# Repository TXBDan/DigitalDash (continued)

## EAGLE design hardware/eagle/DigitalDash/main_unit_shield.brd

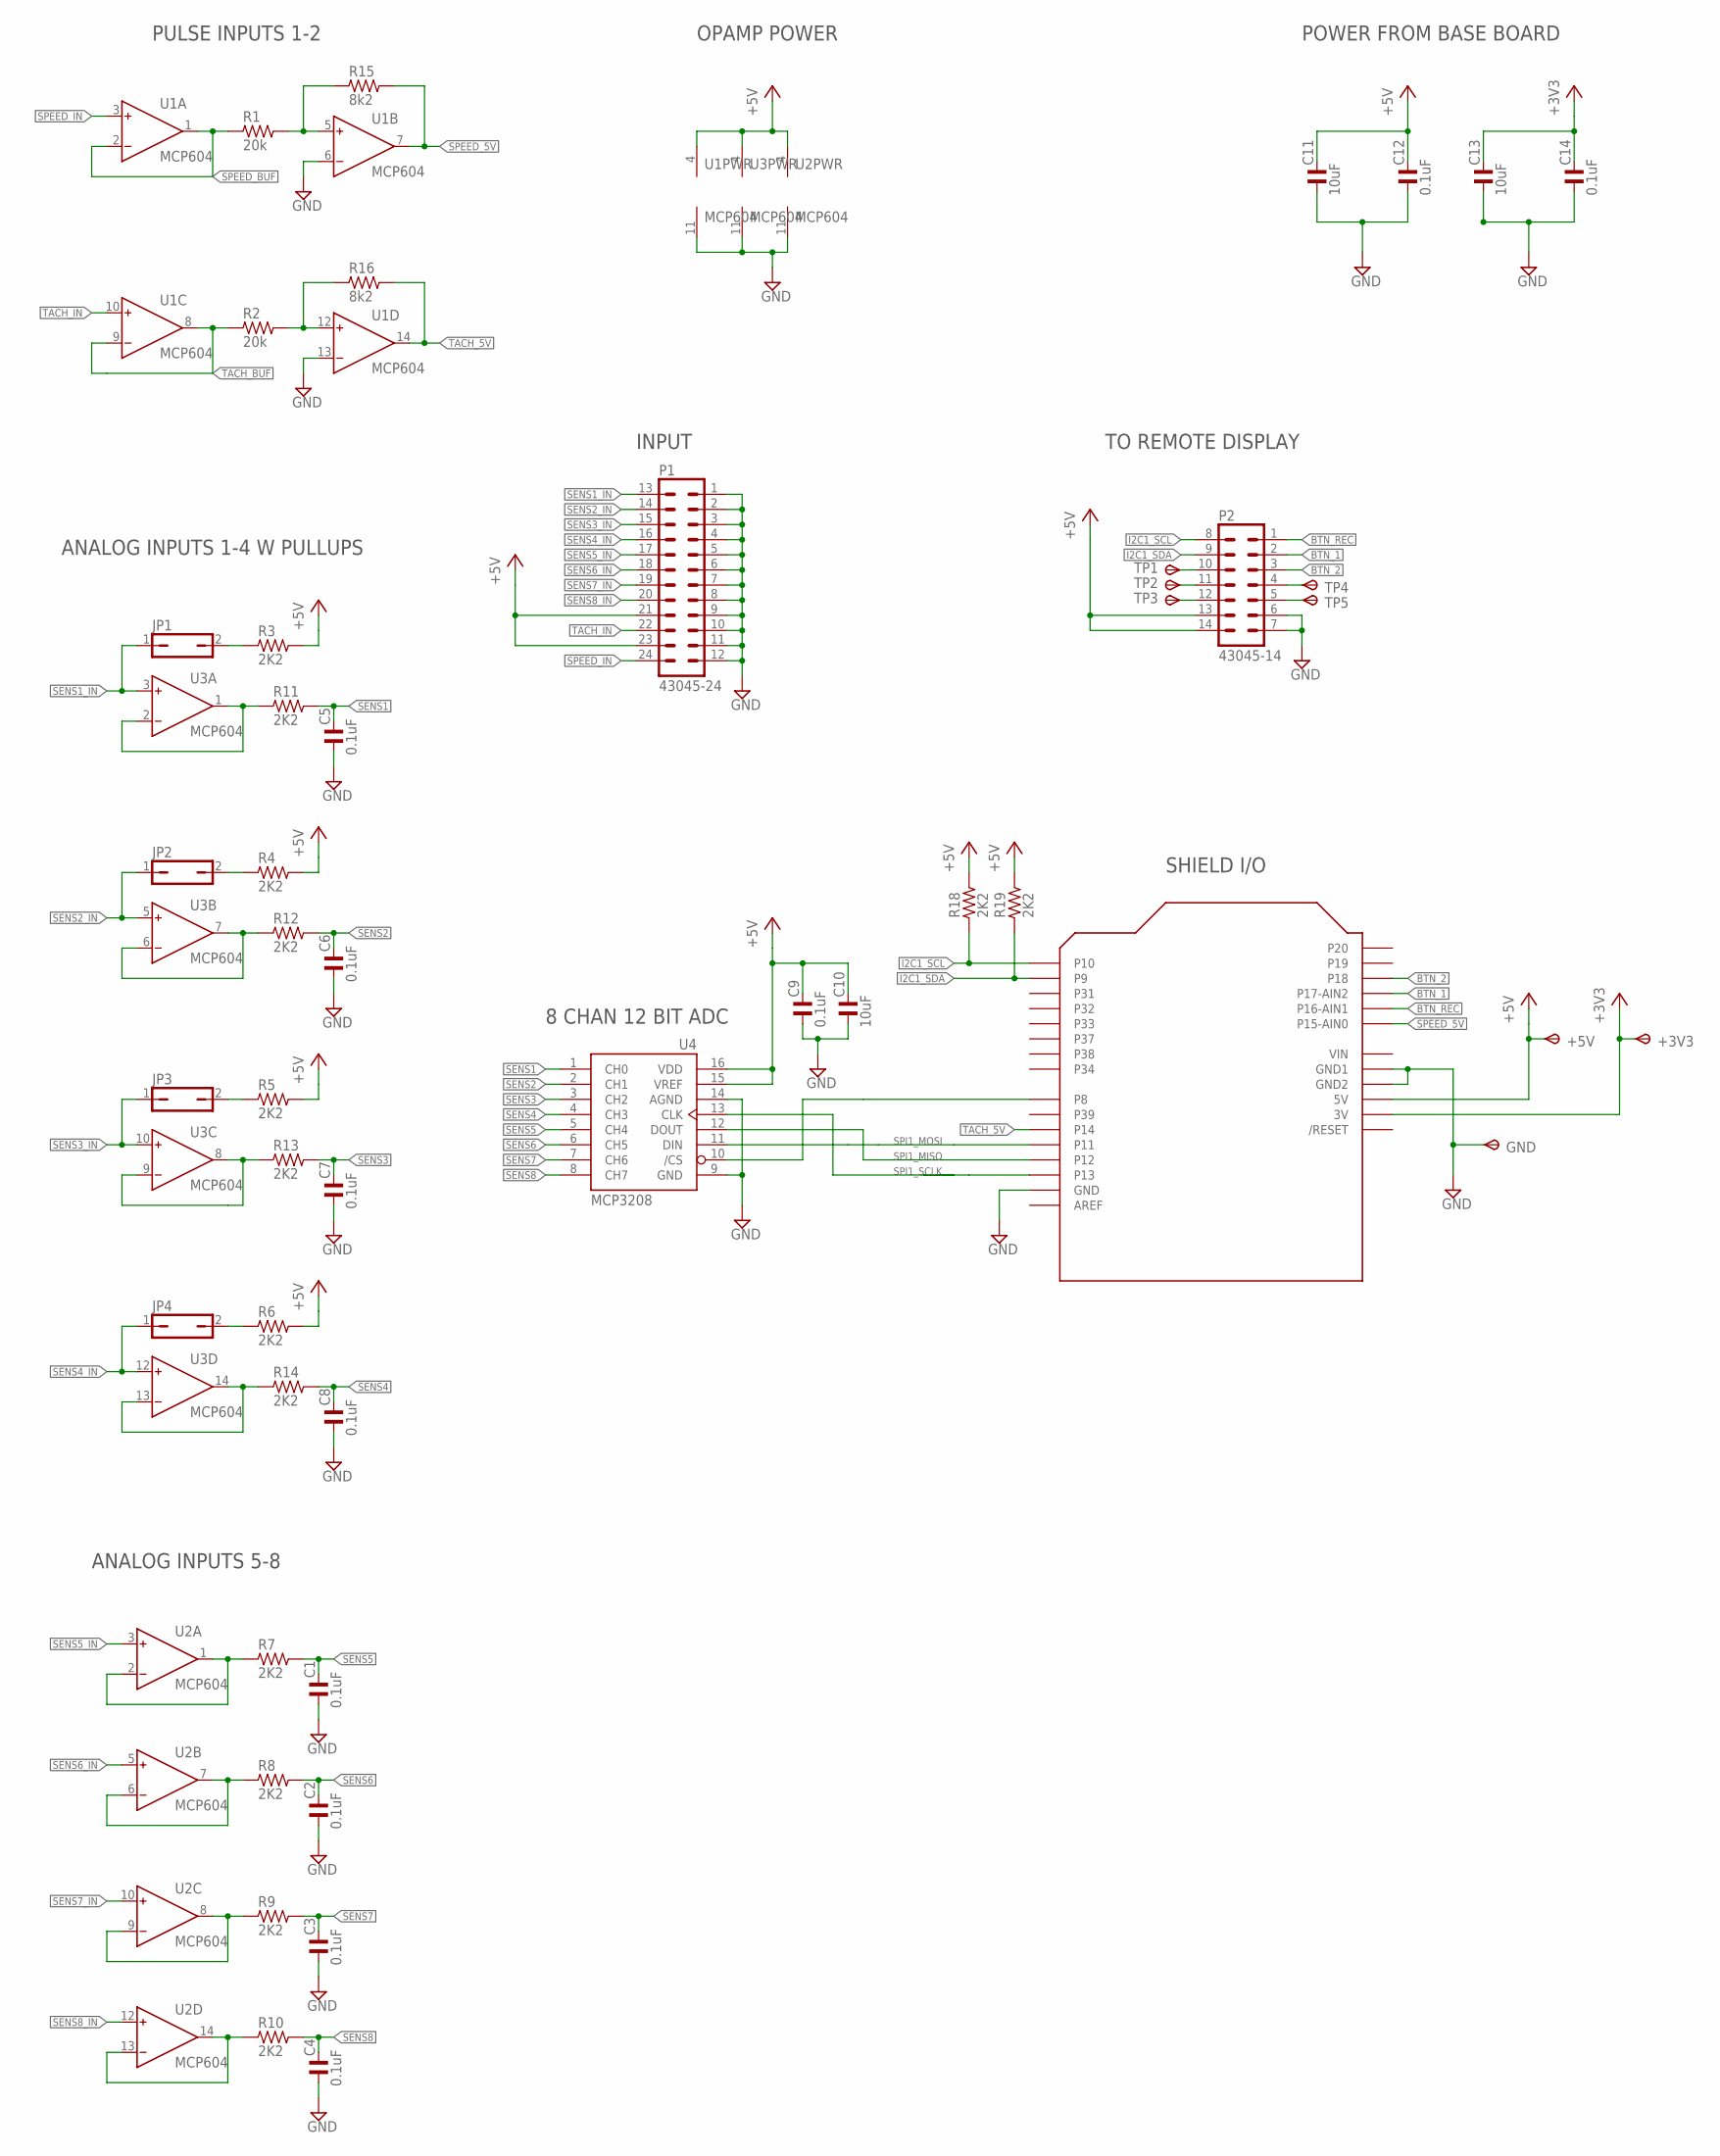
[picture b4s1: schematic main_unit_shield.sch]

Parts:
+3V3, +5V: TPSPAD1-13; P1-13
C1, C2, C3, C4, C5, C6, C7, C8, C9, C12, C14: 0.1uF; C0805; MPN C2012X7R1H104K085AA
C10, C11, C13: 10uF; C0805; MPN C2012X5R1E106K125AB
GND: TPSPAD1-13; P1-13
JP1, JP2, JP3, JP4: JP1Q; JP1; MPN 969102-0000-DA
P1: 43045-24; MPN 43045-2400
P2: 43045-14; MPN 43045-1400
R1, R2: 20k; R0805; MPN CRCW080520K0FKEA
R3, R4, R5, R6, R7, R8, R9, R10, R11, R12, R13, R14, R18, R19: 2K2; R0805; MPN CRCW08052K20FKEA
R15, R16: 8k2; R0805; MPN CRCW08058K20FKEAHP
TP1, TP2, TP3, TP4, TP5: TPSPAD1-13; P1-13
U1, U2, U3: MCP604; SO14; MPN MCP6044-E/SL
U4: MCP3208; SO16; MPN MCP3208-BI/SL
U5: ARDUINOUNO; ARDUINO

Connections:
+3V3: +3V3.TP, C13.2, C14.2, U5.3V
+5V: +5V.TP, C9.2, C10.2, C11.2, C12.2, P1.21, P1.23, P2.13, P2.14, R3.2, R4.2, R5.2, R6.2, R18.2, R19.2, U1.4 (V+), U2.4 (V+), U3.4 (V+), U4.15 (VREF), U4.16 (VDD), U5.5V
BTN_1: P2.2, U5.A2 (P17-AIN2)
BTN_2: P2.3, U5.A3 (P18)
BTN_REC: P2.1, U5.A1 (P16-AIN1)
GND: C1.1, C2.1, C3.1, C4.1, C5.1, C6.1, C7.1, C8.1, C9.1, C10.1, C11.1, C12.1, C13.1, C14.1, GND.TP, P1.1, P1.2, P1.3, P1.4, P1.5, P1.6, P1.7, P1.8, P1.9, P1.10, P1.11, P1.12, P2.6, P2.7, U1.6 (IN-), U1.11 (V-), U1.13 (IN-), U2.11 (V-), U3.11 (V-), U4.9 (GND), U4.14 (AGND), U5.GND, U5.GND1, U5.GND2
I2C1_SCL: P2.8, R18.1, U5.D0 (P10)
I2C1_SDA: P2.9, R19.1, U5.D1 (P9)
unnamed: R1.2, R15.1, U1.5 (IN+)
unnamed: R2.2, R16.1, U1.12 (IN+)
unnamed: U4.10 (/CS), U5.D8 (P8)
unnamed: JP1.2, R3.1
unnamed: JP3.2, R5.1
unnamed: P2.10, TP1.TP
unnamed: P2.11, TP2.TP
unnamed: JP2.2, R4.1
unnamed: P2.12, TP3.TP
unnamed: JP4.2, R6.1
unnamed: P2.4, TP4.TP
unnamed: P2.5, TP5.TP
SENS1: C5.2, R11.2, U4.1 (CH0)
SENS1_BUF: R11.1, U3.1 (OUT), U3.2 (IN-)
SENS1_IN: JP1.1, P1.13, U3.3 (IN+)
SENS2: C6.2, R12.2, U4.2 (CH1)
SENS2_BUF: R12.1, U3.6 (IN-), U3.7 (OUT)
SENS2_IN: JP2.1, P1.14, U3.5 (IN+)
SENS3: C7.2, R13.2, U4.3 (CH2)
SENS3_BUF: R13.1, U3.8 (OUT), U3.9 (IN-)
SENS3_IN: JP3.1, P1.15, U3.10 (IN+)
SENS4: C8.2, R14.2, U4.4 (CH3)
SENS4_BUF: R14.1, U3.13 (IN-), U3.14 (OUT)
SENS4_IN: JP4.1, P1.16, U3.12 (IN+)
SENS5: C1.2, R7.2, U4.5 (CH4)
SENS5_BUF: R7.1, U2.1 (OUT), U2.2 (IN-)
SENS5_IN: P1.17, U2.3 (IN+)
SENS6: C2.2, R8.2, U4.6 (CH5)
SENS6_BUF: R8.1, U2.6 (IN-), U2.7 (OUT)
SENS6_IN: P1.18, U2.5 (IN+)
SENS7: C3.2, R9.2, U4.7 (CH6)
SENS7_BUF: R9.1, U2.8 (OUT), U2.9 (IN-)
SENS7_IN: P1.19, U2.10 (IN+)
SENS8: C4.2, R10.2, U4.8 (CH7)
SENS8_BUF: R10.1, U2.13 (IN-), U2.14 (OUT)
SENS8_IN: P1.20, U2.12 (IN+)
SPEED_5V: R15.2, U1.7 (OUT), U5.A0 (P15-AIN0)
SPEED_BUF: R1.1, U1.1 (OUT), U1.2 (IN-)
SPEED_IN: P1.24, U1.3 (IN+)
SPI1_MISO: U4.12 (DOUT), U5.D12 (P12)
SPI1_MOSI: U4.11 (DIN), U5.D11 (P11)
SPI1_SCLK: U4.13 (CLK), U5.D13 (P13)
TACH_5V: R16.2, U1.14 (OUT), U5.D10 (P14)
TACH_BUF: R2.1, U1.8 (OUT), U1.9 (IN-)
TACH_IN: P1.22, U1.10 (IN+)
VIN: U5.VIN

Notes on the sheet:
ANALOG INPUTS 1-4 W PULLUPS
PULSE INPUTS 1-2
TO REMOTE DISPLAY
SHIELD I/O
8 CHAN 12 BIT ADC
OPAMP POWER
POWER FROM BASE BOARD
ANALOG INPUTS 5-8
INPUT

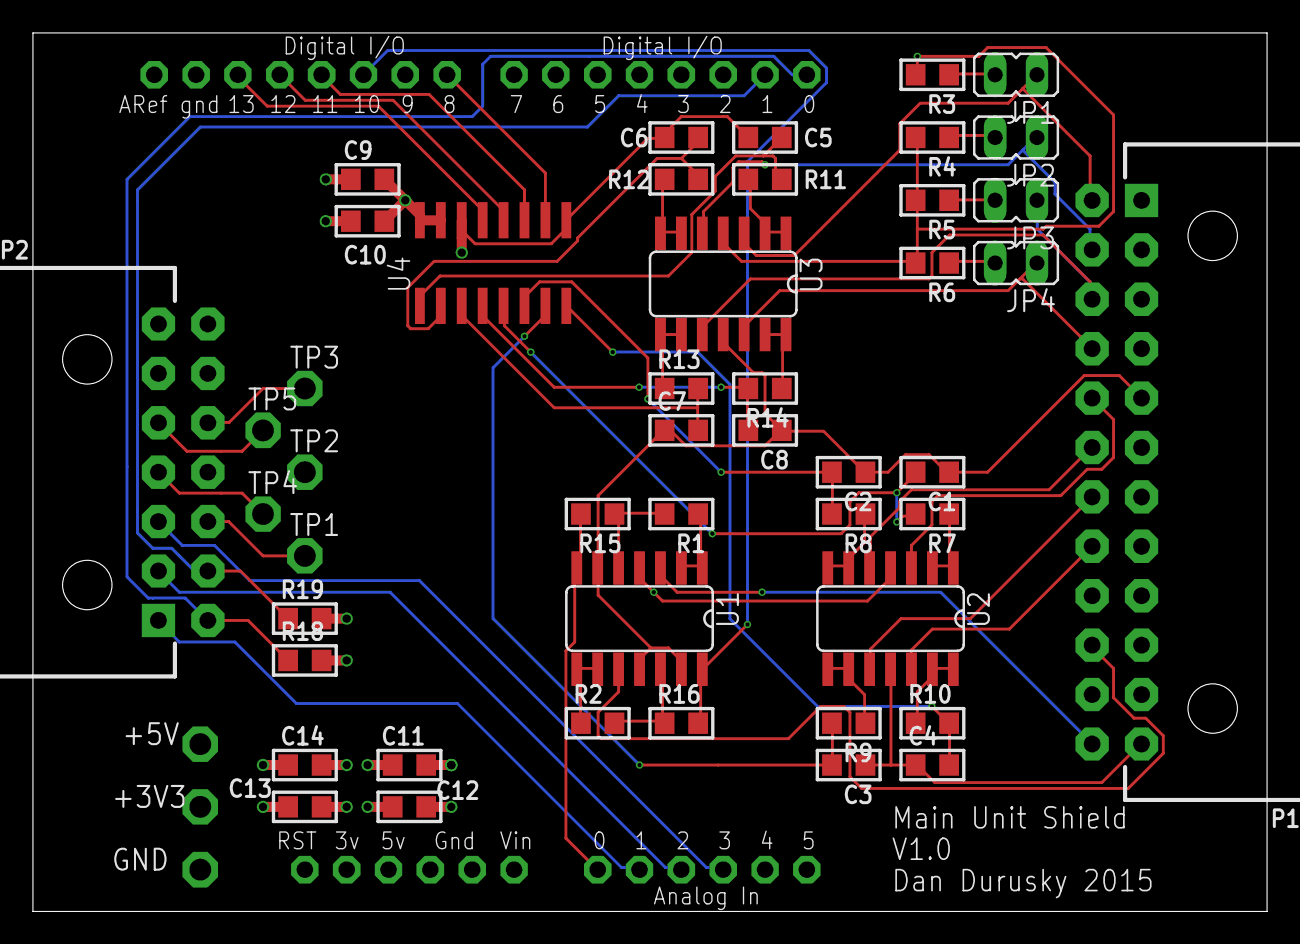
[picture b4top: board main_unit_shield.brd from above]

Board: 4 copper layers, 74.9 x 53.3 mm, 51 parts (0 on the bottom side), 53 nets.

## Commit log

2024-05-17 initial upload
    uploading here to archive
2024-05-17 added in car pic
